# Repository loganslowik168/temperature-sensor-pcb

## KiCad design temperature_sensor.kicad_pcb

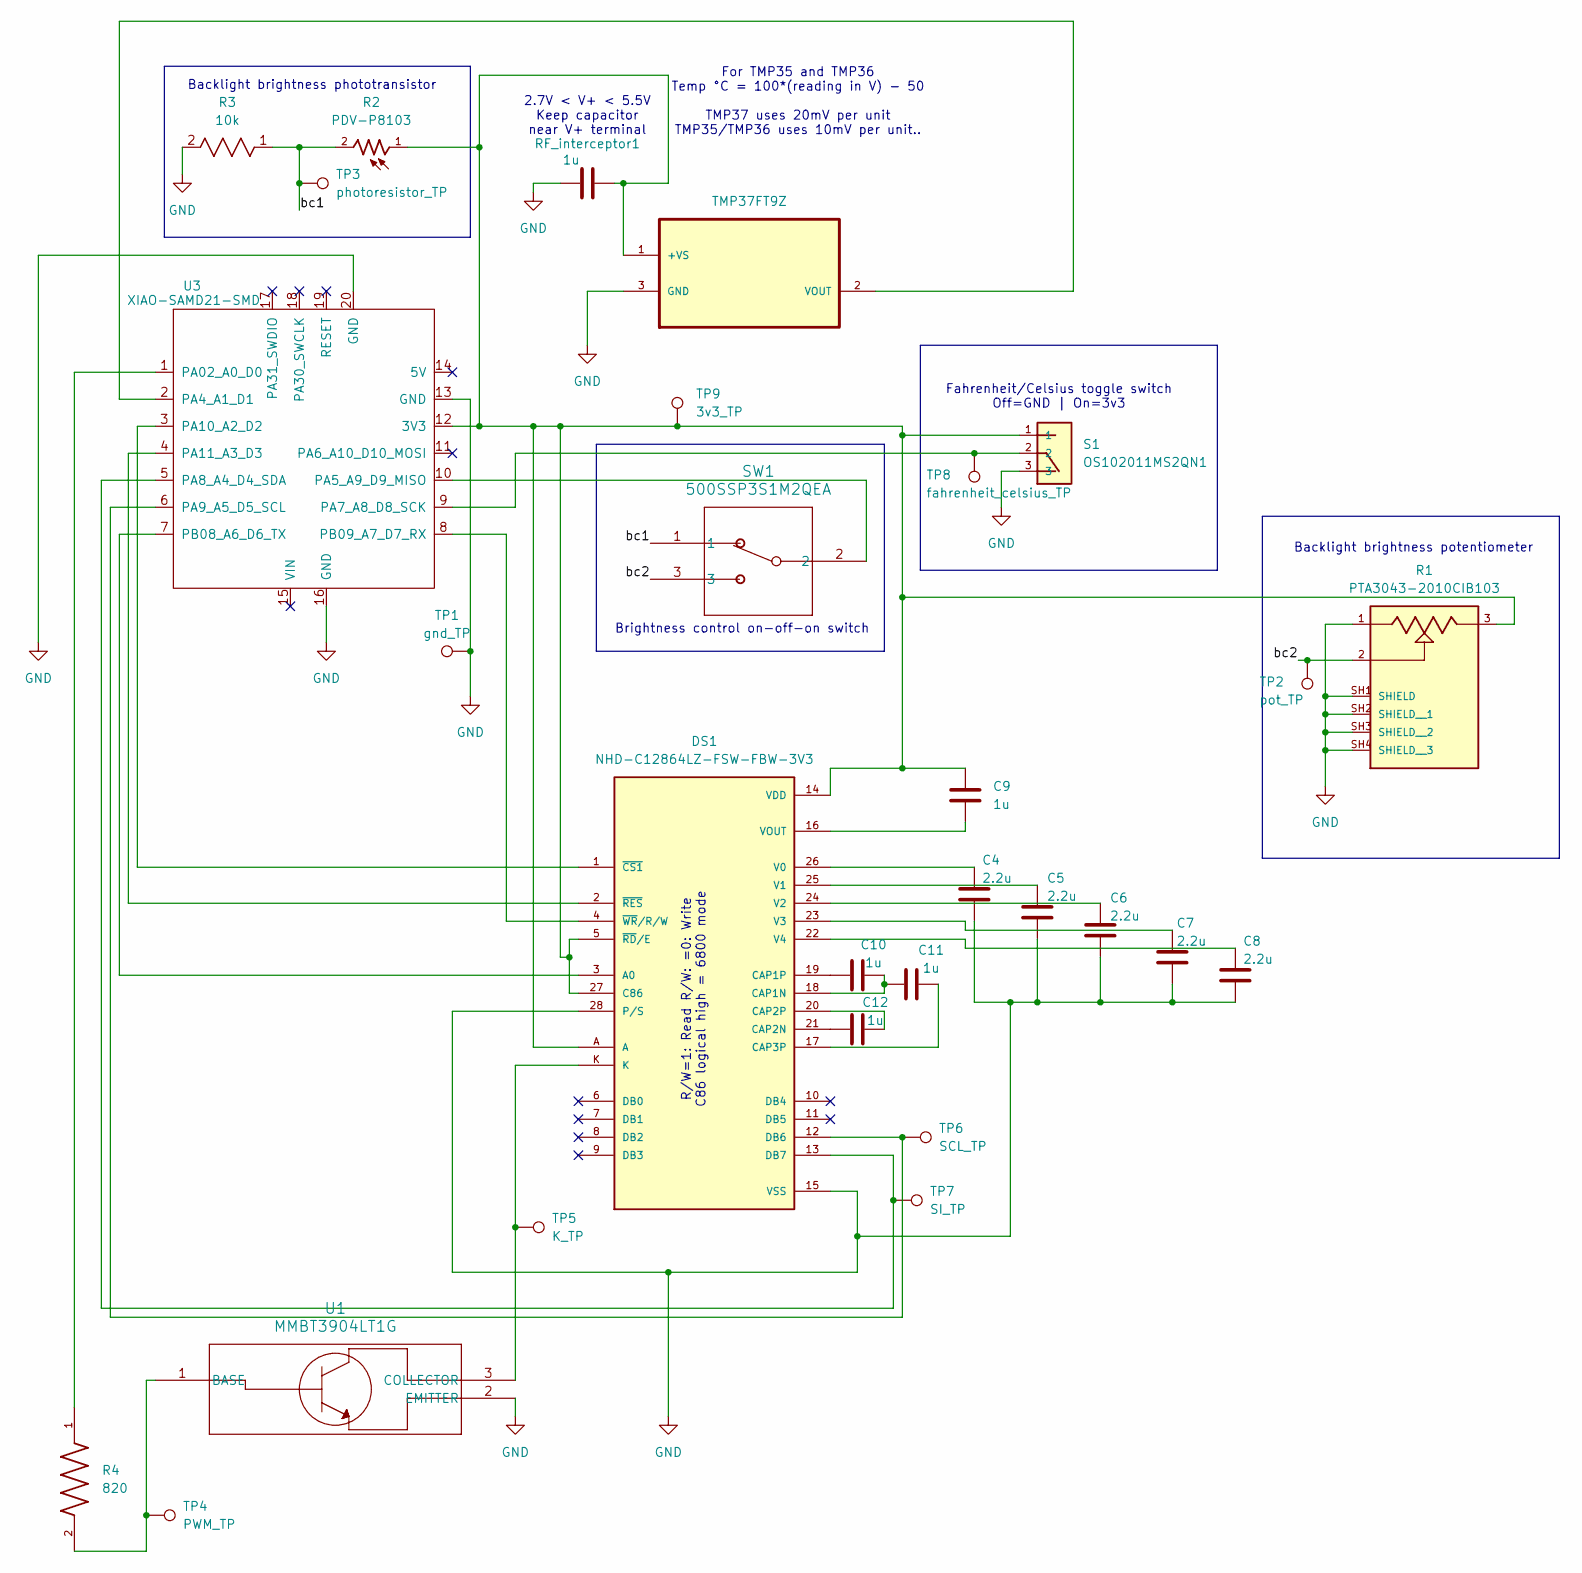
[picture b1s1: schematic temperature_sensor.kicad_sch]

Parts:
C4, C5, C6, C7, C8: 2.2u; C_0603_1608Metric_Pad1.08x0.95mm_HandSolder
C9, C10, C11, C12: 1u; C_0603_1608Metric_Pad1.08x0.95mm_HandSolder
DS1: NHD-C12864LZ-FSW-FBW-3V3; LCD_NHD-C12864LZ-FSW-FBW-3V3; PARTREV 1.0
R1: PTA3043-2010CIB103; slide_potentiometer; PARTREV 04/21
R2: PDV-P8103; photoresistor; PARTREV 3/30/06
R3: 10k; YAG_MF25_YAG
R4: 820; RESC6332X65N
RF_interceptor1: 1u; C_0603_1608Metric_Pad1.08x0.95mm_HandSolder
S1: OS102011MS2QN1; slideSwitch
SW1: 500SSP3S1M2QEA; onOffOn
TP1: gnd_TP; Pin_D1.0mm_L10.0mm
TP2: pot_TP; Pin_D1.0mm_L10.0mm
TP3: photoresistor_TP; Pin_D1.0mm_L10.0mm
TP4: PWM_TP; Pin_D1.0mm_L10.0mm
TP5: K_TP; Pin_D1.0mm_L10.0mm
TP6: SCL_TP; Pin_D1.0mm_L10.0mm
TP7: SI_TP; Pin_D1.0mm_L10.0mm
TP8: fahrenheit_celsius_TP; Pin_D1.0mm_L10.0mm
TP9: 3v3_TP; Pin_D1.0mm_L10.0mm
U1: MMBT3904LT1G; SOT-23_3L_ONS
U3: XIAO-SAMD21-SMD
U5: TMP37FT9Z; MPN TMP37FT9Z

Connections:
/bc1: R2.2, R3.1, SW1.1, TP3.1
/bc2: R1.2, SW1.3, TP2.1
GND: C4.1, C5.1, C6.1, C7.1, C8.1, DS1.15 (VSS), DS1.28 (P/S), R1.1, R1.SH1 (SHIELD), R1.SH2 (SHIELD__1), R1.SH3 (SHIELD__2), R1.SH4 (SHIELD__3), R3.2, RF_interceptor1.1, S1.3, TP1.1, U1.2 (EMITTER), U3.13 (GND), U3.16 (GND), U3.20 (GND), U5.3 (GND)
unnamed: DS1.3 (A0), U3.7 (PB08_A6_D6_TX)
unnamed: C9.2, DS1.5 (~RD/E), DS1.14 (VDD), DS1.27 (C86), DS1.A, R1.3, R2.1, RF_interceptor1.2, S1.1, TP9.1, U3.12 (3V3), U5.1 (+VS)
unnamed: C10.2, C11.1, DS1.18 (CAP1N)
unnamed: C10.1, DS1.19 (CAP1P)
unnamed: C12.1, DS1.21 (CAP2N)
unnamed: C12.2, DS1.20 (CAP2P)
unnamed: C11.2, DS1.17 (CAP3P)
unnamed: DS1.12 (DB6), TP6.1, U3.6 (PA9_A5_D5_SCL)
unnamed: DS1.13 (DB7), TP7.1, U3.5 (PA8_A4_D4_SDA)
unnamed: C4.2, DS1.26 (V0)
unnamed: C5.2, DS1.25 (V1)
unnamed: C6.2, DS1.24 (V2)
unnamed: C7.2, DS1.23 (V3)
unnamed: C8.2, DS1.22 (V4)
unnamed: C9.1, DS1.16 (VOUT)
unnamed: DS1.1 (~CS1), U3.3 (PA10_A2_D2)
unnamed: DS1.2 (~RES), U3.4 (PA11_A3_D3)
unnamed: DS1.4 (~WR/R/W), U3.8 (PB09_A7_D7_RX)
unnamed: R4.2, TP4.1, U1.1 (BASE)
unnamed: DS1.K, TP5.1, U1.3 (COLLECTOR)
unnamed: R4.1, U3.1 (PA02_A0_D0)
unnamed: U3.2 (PA4_A1_D1), U5.2 (VOUT)
unnamed: SW1.2, U3.10 (PA5_A9_D9_MISO)
unnamed: S1.2, TP8.1, U3.9 (PA7_A8_D8_SCK)

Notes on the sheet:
2.7V < V+ < 5.5V Keep capacitor near V+ terminal
Fahrenheit/Celsius toggle switch Off=GND | On=3v3
R/W=1: Read R/W: =0: Write C86 logical high = 6800 mode
Backlight brightness phototransistor
Backlight brightness potentiometer
Brightness control on-off-on switch
For TMP35 and TMP36 Temp °C = 100*(reading in V) - 50 TMP37 uses 20mV per unit TMP35/TMP36 uses 10mV per unit..

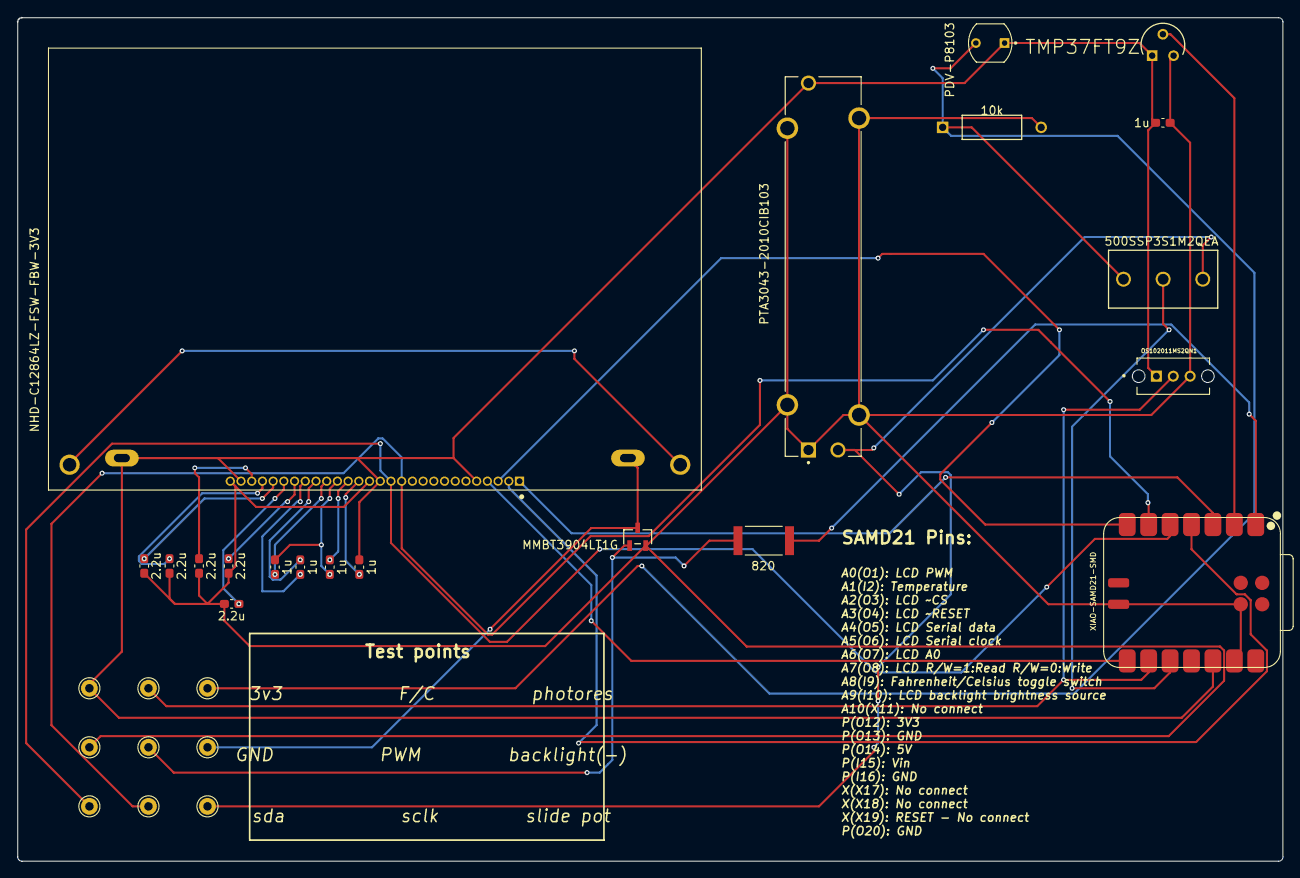
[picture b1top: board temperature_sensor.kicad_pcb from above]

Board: 2 copper layers, 149.9 x 99.9 mm, 29 parts (0 on the bottom side), 27 nets.

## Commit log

2025-03-26 both usb-c and micocontroller. changing to just the one design
2025-03-26 gonna change c to f conversion in digital instead of logically. this avoids the need to calculate current over Vout(-)'s voltage divider
2025-03-26 lol this circuit got so much simpler
2025-03-27 i need to revert some of this to get my old stuff back lol
2025-03-27 ok yeah no
2025-03-27 this is the one. simple and easy
2025-03-28 LCD screen. need to verify pins. may need to swap to SPI if i cant hold ~CS1 low
2025-04-13 added potentiometer, photoresistor, switch between the two and off, and added a F/C switch. need to up current into LCD's A pin
2025-04-13 got everything except the MOSFET to step up the current to 80mA. all footprints added
2025-04-14 this should be good to ship but i want to add some LEDs and some test points
2025-04-14 ready for PCB design
2025-04-14 initial pcb design
2025-04-14 sent for prod v1.0
